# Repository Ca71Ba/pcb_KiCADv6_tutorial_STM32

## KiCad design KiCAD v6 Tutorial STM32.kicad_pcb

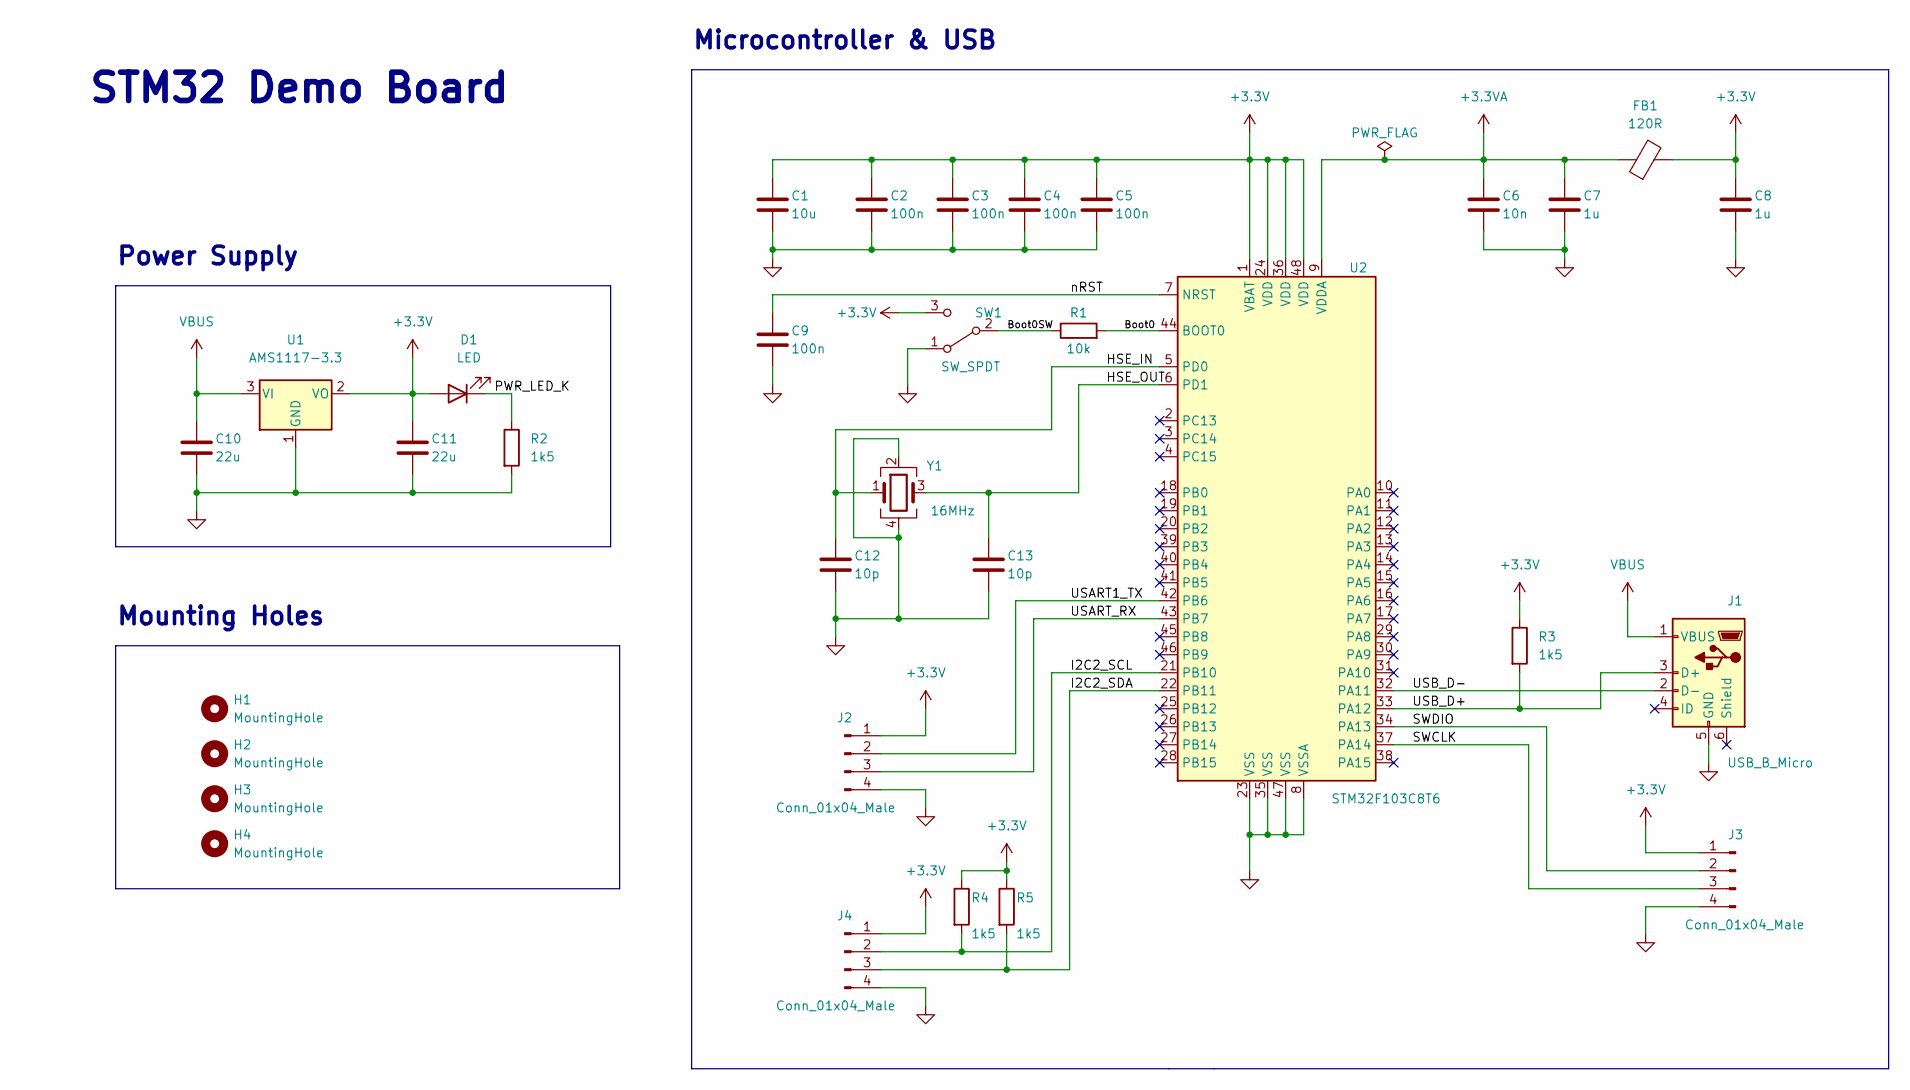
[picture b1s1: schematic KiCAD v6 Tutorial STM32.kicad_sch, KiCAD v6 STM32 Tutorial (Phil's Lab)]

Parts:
C1: 10u; C_0805_2012Metric
C2, C3, C4, C5, C9: 100n; C_0402_1005Metric
C6: 10n; C_0402_1005Metric
C7, C8: 1u; C_0402_1005Metric
C10, C11: 22u; C_0805_2012Metric
C12, C13: 10p; C_0402_1005Metric
D1: LED; LED_0603_1608Metric
FB1: 120R; L_0603_1608Metric
H1, H2, H3, H4: MountingHole; MountingHole_2.2mm_M2
J1: USB_B_Micro; USB_Micro-B_Wuerth_629105150521
J2, J3, J4: Conn_01x04_Male; PinHeader_1x04_P2.54mm_Vertical
R1: 10k; R_0402_1005Metric
R2, R3, R4, R5: 1k5; R_0402_1005Metric
SW1: SW_SPDT; SW_SPDT_PCM12
U1: AMS1117-3.3; SOT-223-3_TabPin2
U2: STM32F103C8T6; LQFP-48_7x7mm_P0.5mm
Y1: 16MHz; Crystal_SMD_3225-4Pin_3.2x2.5mm

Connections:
+3.3V: C1.1, C2.1, C3.1, C4.1, C5.1, C8.1, C11.1, D1.2 (A), FB1.2, J2.1, J3.1, J4.1, R3.1, R4.1, R5.1, SW1.3 (C), U1.2 (VO), U2.1 (VBAT), U2.24 (VDD), U2.36 (VDD), U2.48 (VDD)
+3.3VA: C6.1, C7.1, FB1.1, U2.9 (VDDA)
/Boot0: R1.2, U2.44 (BOOT0)
/Boot0SW: R1.1, SW1.2 (B)
/HSE_IN: C12.1, U2.5 (PD0), Y1.1
/HSE_OUT: C13.1, U2.6 (PD1), Y1.3
/I2C2_SCL: J4.2, R4.2, U2.21 (PB10)
/I2C2_SDA: J4.3, R5.2, U2.22 (PB11)
/PWR_LED_K: D1.1 (K), R2.1
/SWCLK: J3.3, U2.37 (PA14)
/SWDIO: J3.2, U2.34 (PA13)
/USART1_TX: J2.2, U2.42 (PB6)
/USART_RX: J2.3, U2.43 (PB7)
/USB_D+: J1.3 (D+), R3.2, U2.33 (PA12)
/USB_D-: J1.2 (D-), U2.32 (PA11)
/nRST: C9.1, U2.7 (NRST)
GND: C1.2, C2.2, C3.2, C4.2, C5.2, C6.2, C7.2, C8.2, C9.2, C10.2, C11.2, C12.2, C13.2, J1.5 (GND), J2.4, J3.4, J4.4, R2.2, SW1.1 (A), U1.1 (GND), U2.8 (VSSA), U2.23 (VSS), U2.35 (VSS), U2.47 (VSS), Y1.2, Y1.4
VBUS: C10.1, J1.1 (VBUS), U1.3 (VI)

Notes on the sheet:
STM32 Demo Board
Power Supply
Mounting Holes
Microcontroller & USB

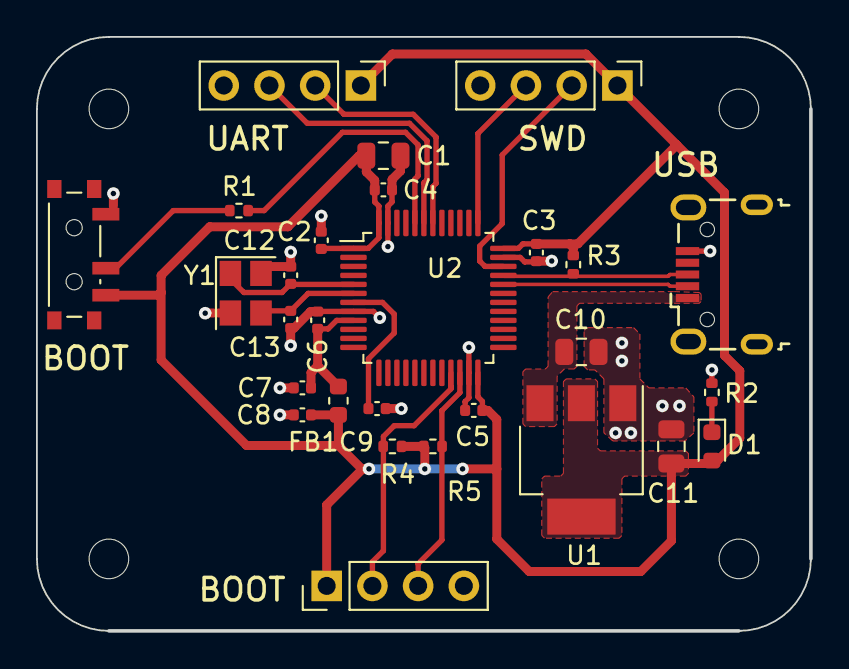
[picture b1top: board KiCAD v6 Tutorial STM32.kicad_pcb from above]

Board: 2 copper layers, 43.0 x 33.0 mm, 32 parts (0 on the bottom side), 18 nets.

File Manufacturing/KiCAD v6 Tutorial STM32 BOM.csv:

"Source:","/Users/carsten/Embedded/PCD Design/KiCAD v6 Tutorial STM32/KiCAD v6 Tutorial STM32/KiCAD v6 Tutorial STM32.kicad_sch"
"Date:","2022 December 10, Saturday 18:51:30"
"Tool:","Eeschema (6.0.9-0)"
"Generator:","/Applications/KiCad/KiCad.app/Contents/SharedSupport/plugins/bom_csv_grouped_by_value_with_fp.py"
"Component Count:","32"
"Ref","Qnty","Value","Cmp name","Footprint","Description","Vendor"
"C1, ","1","10u","C","Capacitor_SMD:C_0805_2012Metric","Unpolarized capacitor",""
"C2, C3, C4, C5, C9, ","5","100n","C","Capacitor_SMD:C_0402_1005Metric","Unpolarized capacitor",""
"C6, ","1","10n","C","Capacitor_SMD:C_0402_1005Metric","Unpolarized capacitor",""
"C7, C8, ","2","1u","C","Capacitor_SMD:C_0402_1005Metric","Unpolarized capacitor",""
"C10, C11, ","2","22u","C","Capacitor_SMD:C_0805_2012Metric","Unpolarized capacitor",""
"C12, C13, ","2","10p","C","Capacitor_SMD:C_0402_1005Metric","Unpolarized capacitor",""
"D1, ","1","LED","LED","LED_SMD:LED_0603_1608Metric","Light emitting diode",""
"FB1, ","1","120R","FerriteBead","Inductor_SMD:L_0603_1608Metric","Ferrite bead",""
"H1, H2, H3, H4, ","4","MountingHole","MountingHole","MountingHole:MountingHole_2.2mm_M2","Mounting Hole without connection",""
"J1, ","1","USB_B_Micro","USB_B_Micro","Connector_USB:USB_Micro-B_Wuerth_629105150521","USB Micro Type B connector",""
"J2, J3, J4, ","3","Conn_01x04_Male","Conn_01x04_Male","Connector_PinHeader_2.54mm:PinHeader_1x04_P2.54mm_Vertical","Generic connector, single row, 01x04, script generated (kicad-library-utils/schlib/autogen/connector/)",""
"R1, ","1","10k","R","Resistor_SMD:R_0402_1005Metric","Resistor",""
"R2, R3, R4, R5, ","4","1k5","R","Resistor_SMD:R_0402_1005Metric","Resistor",""
"SW1, ","1","SW_SPDT","SW_SPDT","Button_Switch_SMD:SW_SPDT_PCM12","Switch, single pole double throw",""
"U1, ","1","AMS1117-3.3","AMS1117-3.3","Package_TO_SOT_SMD:SOT-223-3_TabPin2","1A Low Dropout regulator, positive, 3.3V fixed output, SOT-223",""
"U2, ","1","STM32F103C8T6","STM32F103C8Tx","Package_QFP:LQFP-48_7x7mm_P0.5mm","ARM Cortex-M3 MCU, 64KB flash, 20KB RAM, 72MHz, 2-3.6V, 37 GPIO, LQFP-48",""
"Y1, ","1","16MHz","Crystal_GND24","Crystal:Crystal_SMD_3225-4Pin_3.2x2.5mm","Four pin crystal, GND on pins 2 and 4",""

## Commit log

2023-01-08 Initial Load
